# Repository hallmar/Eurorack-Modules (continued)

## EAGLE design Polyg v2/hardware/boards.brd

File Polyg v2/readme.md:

# Polyg v2 8-Voice Midi synth

This new version has a dedicated MIDI thru instead of routing it into the Teensy and back out. 
And it has alot of improvements of the hardware.

[Youtube demo](https://www.youtube.com/watch?v=QhJZFhLLbBc&feature=youtu.be)

[Mouser cart](https://www.mouser.com/ProjectManager/ProjectDetail.aspx?AccessID=3288d77cba)

8 Voice polyphonic synthesizer with selectable Karplus strong(8 voice plucky string synth) or a 8 voice FM synth with square,sine,triangle and sawtooth. It has a basic FM(techincally Phase Modulation, like the DX7) with one Modulator. 
There's an index knob to set the ratio, decay for the operator and the amount of FM applied.

Current hardware uses a high quality 16bit/44.1kHz DAC(CD4334).

It has MIDI IN and MIDI OUT/THRU. It uses the Arturia Standard for DIN to stereo jack, so type B midi.
You can find adapters in almost every synthstore now. 

## Where/how to order
I won't have any PCB's in stock any time soon. This project is pretty much abandoned.
You have my approval of making your own, just remember to credit me.

## Designed With

* Eagle CAD
* Arduino IDE
* Audio System Design Tool for Teensy Audio Library

## Versioning
* 1.0 - [Hardware] Original PCB batch with wrong silkscreen
* 1.1 - [Hardware] v1 of PCBs
* 1.0 - [Software] Original software release
* 2.0 - [Hardware] v2 of PCB is made with improvements
* 2.0 - [Hardware] v2 of firmware is written
## Authors

* **Hallmar Gauti Halldórsson** 

## License
Hardware: cc-by-sa-3.0

Software: MIT license

But if you want to sell or do something with the software or hardware then it'd be nice to include my name and link to my Github somewhere :)

## Acknowledgments
Alot of the inspiration for this project came from the [String Theory](https://makesynthsnotwar.com/modules/stringtheory/) eurorack module by Make Synths Not War.
The original String Theory was programmed by [Jan Ostman](https://janostman.wordpress.com).

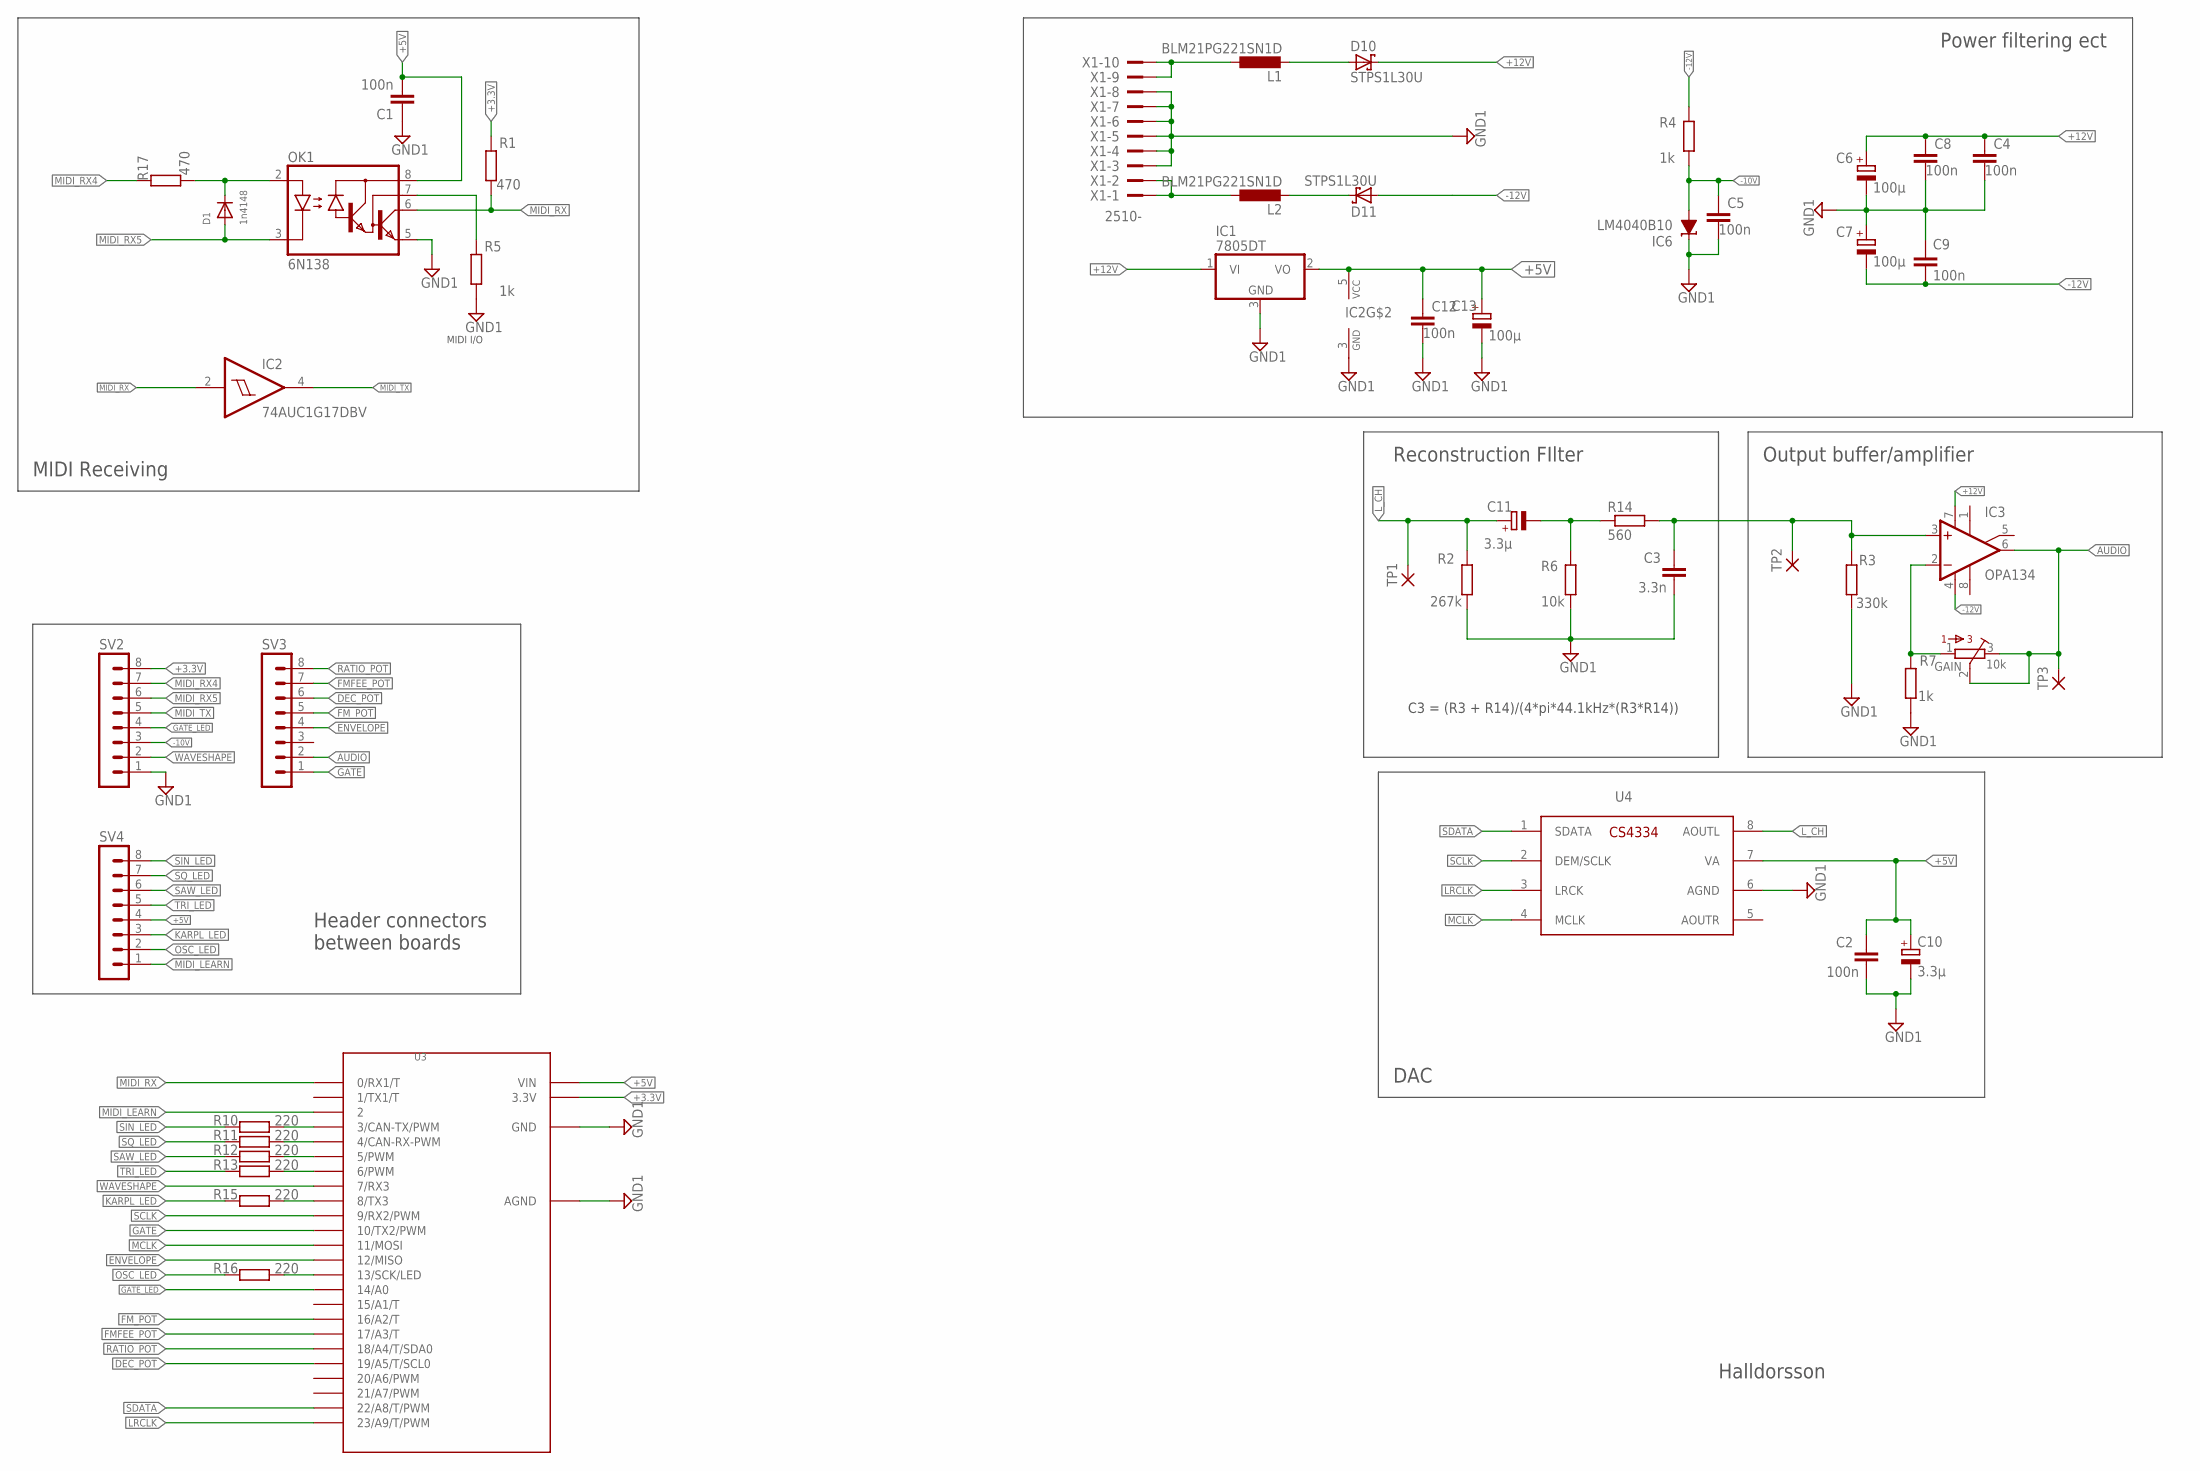
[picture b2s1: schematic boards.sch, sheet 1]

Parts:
C1, C2, C4, C5, C8, C9, C12: 100n; C1206
C3: 3.3n; C1206
C6, C7, C13: 100µ; 153CLV-0505
C10, C11: 3.3µ; 153CLV-0405
D1: 1n4148; SOD-123
D10, D11: STPS1L30U; SMB
GAIN: 10k; BOURNS_3362P_TRIMMER
IC1: 7805DT; TO252
IC2: 74AUC1G17DBV; SOT23-5
IC3: OPA134; SO08
IC6: LM4040B10; DBZ_R-PDSO-G3
L1, L2: BLM21PG221SN1D; L2012C
OK1: 6N138; DIL08
R1, R17: 470; M1206
R2: 267k; M1206
R3: 330k; M1206
R4, R5, R7: 1k; M1206
R6: 10k; M1206
R10, R11, R12, R13, R15, R16: 220; M1206
R14: 560; M1206
SV2, SV3, SV4: MA08-1
TP1, TP2, TP3: 2,54/1,0
U3: TEENSY3.2.BAREBONES; TEENSY3.2_BAREBONES
U4: CS4334; SOIC127P600X175-8N
X1: 2510-; PAK100/2500-10

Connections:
+3.3V: R1.2, SV2.8, U3.3.3V
+5V: C1.2, C2.1, C10.+, C12.1, C13.+, IC1.2 (VO), IC2.5 (VCC), OK1.8 (VCC), SV4.4, U3.VIN, U4.7 (VA)
+12V: C4.1, C6.+, C8.1, D10.C, IC1.1 (VI), IC3.7 (V+)
-10V: C5.1, IC6.2 (A), R4.2, SV2.3
-12V: C7.-, C9.2, D11.A, IC3.4 (V-), R4.1
AUDIO: GAIN.2, GAIN.3, IC3.6 (OUT), SV3.2, TP3.1
DEC_POT: SV3.6, U3.19/A5 (19/A5/T/SCL0)
ENVELOPE: SV3.4, U3.12 (12/MISO)
FMFEE_POT: SV3.7, U3.17/A3 (17/A3/T)
FM_POT: SV3.5, U3.16/A2 (16/A2/T)
GATE: SV3.1, U3.10 (10/TX2/PWM)
GATE_LED: SV2.4, U3.14/A0
GND1: C1.1, C2.2, C3.2, C4.2, C5.2, C6.-, C7.+, C8.2, C9.1, C10.-, C12.2, C13.-, IC1.3 (GND), IC2.3 (GND), IC6.1 (C), OK1.5 (GND), R2.2, R3.2, R5.1, R6.2, R7.2, SV2.1, U3.AGND, U3.GND, U4.6 (AGND), X1.3, X1.4, X1.5, X1.6, X1.7, X1.8
KARPL_LED: R15.2, SV4.3
LRCLK: U3.23/A9 (23/A9/T/PWM), U4.3 (LRCK)
L_CH: C11.+, R2.1, TP1.1, U4.8 (AOUTL)
MCLK: U3.11 (11/MOSI), U4.4 (MCLK)
MIDI_LEARN: SV4.1, U3.2
MIDI_RX: IC2.2 (I), OK1.6 (VO), R1.1, U3.0 (0/RX1/T)
MIDI_RX4: R17.2, SV2.7
MIDI_RX5: D1.A, OK1.3 (C), SV2.6
MIDI_TX: IC2.4 (O), SV2.5
unnamed: C11.-, R6.1, R14.1
unnamed: D1.C, OK1.2 (A), R17.1
unnamed: OK1.7 (VB), R5.2
unnamed: GAIN.1, IC3.2 (-IN), R7.1
unnamed: R16.1, U3.13 (13/SCK/LED)
unnamed: C3.1, IC3.3 (+IN), R3.1, R14.2, TP2.1
unnamed: R10.1, U3.3 (3/CAN-TX/PWM)
unnamed: R11.1, U3.4 (4/CAN-RX-PWM)
unnamed: R12.1, U3.5 (5/PWM)
unnamed: R13.1, U3.6 (6/PWM)
unnamed: R15.1, U3.8 (8/TX3)
unnamed: L1.1, X1.9, X1.10
unnamed: L2.1, X1.1, X1.2
unnamed: D10.A, L1.2
unnamed: D11.C, L2.2
OSC_LED: R16.2, SV4.2
RATIO_POT: SV3.8, U3.18/A4 (18/A4/T/SDA0)
SAW_LED: R12.2, SV4.6
SCLK: U3.9 (9/RX2/PWM), U4.2 (DEM/SCLK)
SDATA: U3.22/A8 (22/A8/T/PWM), U4.1 (SDATA)
SIN_LED: R10.2, SV4.8
SQ_LED: R11.2, SV4.7
TRI_LED: R13.2, SV4.5
WAVESHAPE: SV2.2, U3.7 (7/RX3)

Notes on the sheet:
MIDI I/O
Halldorsson
DAC
Reconstruction FIlter
Header connectors between boards
MIDI Receiving
Power filtering ect
Output buffer/amplifier
C3 = (R3 + R14)/(4*pi*44.1kHz*(R3*R14))

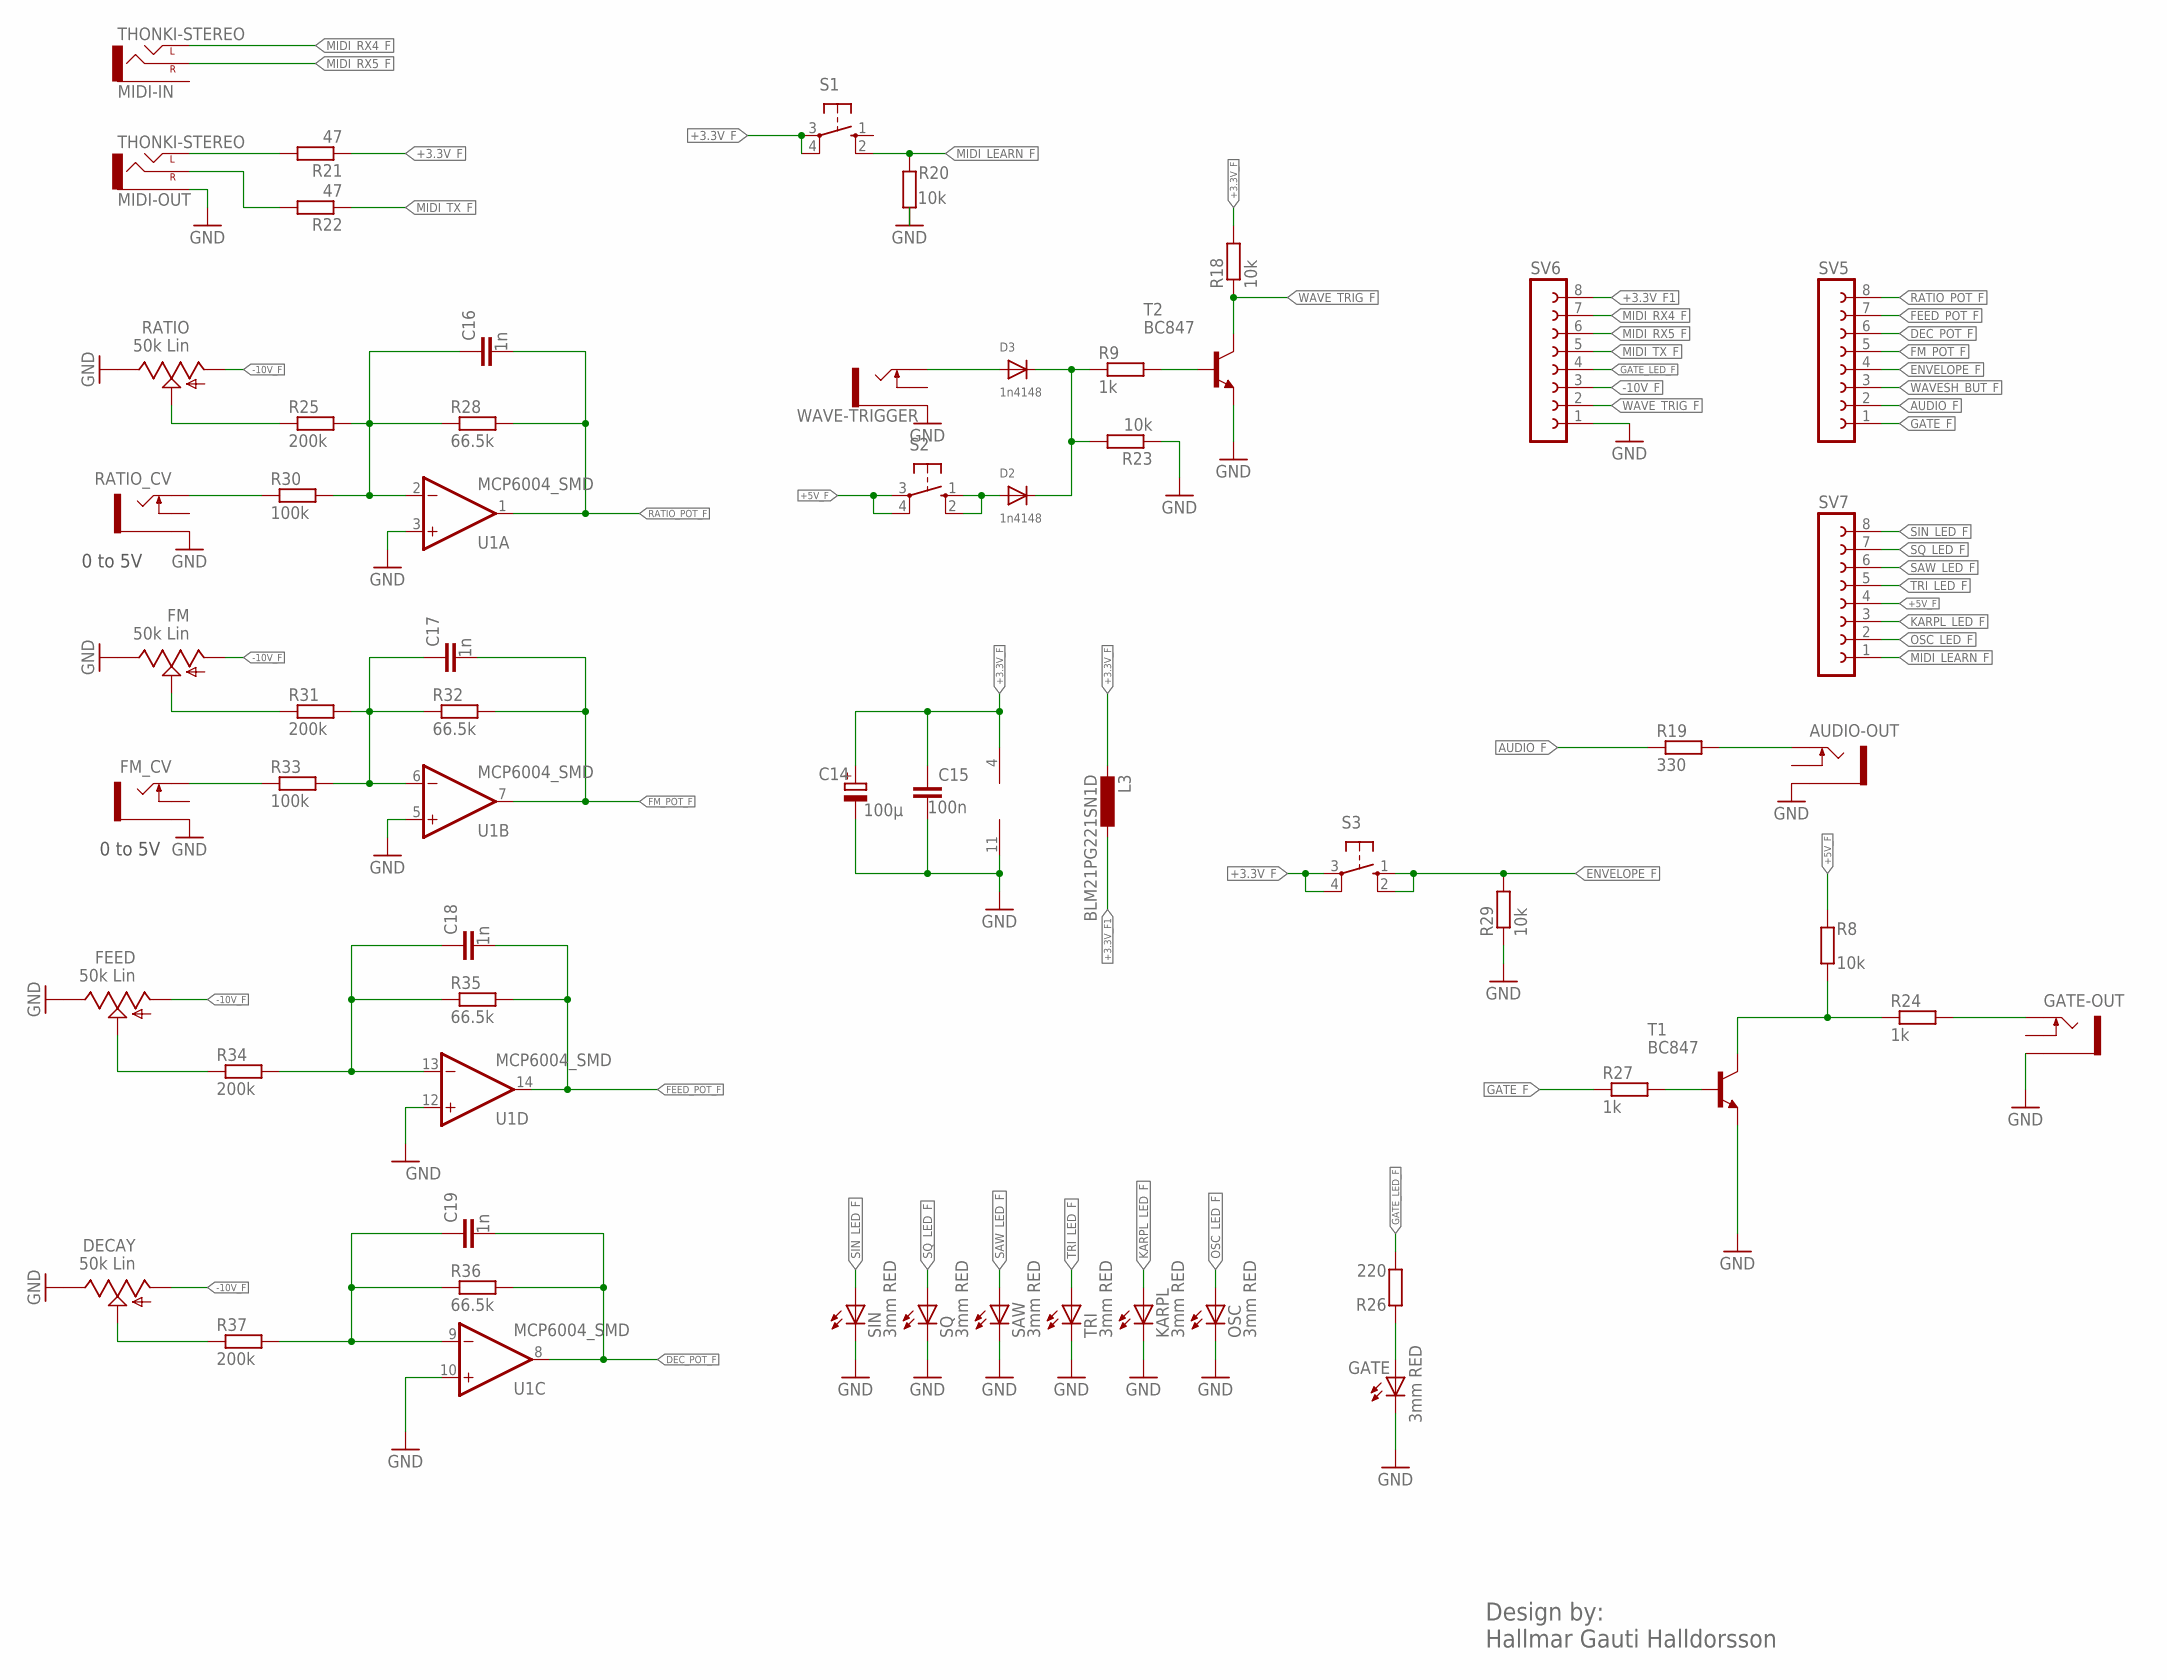
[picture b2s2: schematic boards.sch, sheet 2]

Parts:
AUDIO-OUT: THONKICONNNEW; WQP-PJ301M-12_JACK
C14: 100µ; 153CLV-0505
C15: 100n; C1206
C16, C17, C18, C19: 1n; C1206
D2, D3: 1n4148; SOD-123
DECAY: 50k Lin; 9MM_SNAP-IN_POT
FEED: 50k Lin; 9MM_SNAP-IN_POT
FM: 50k Lin; 9MM_SNAP-IN_POT
FM_CV: THONKICONNNEW; WQP-PJ301M-12_JACK
GATE: 3mm RED; LED3MM
GATE-OUT: THONKICONNNEW; WQP-PJ301M-12_JACK
KARPL: 3mm RED; LED3MM
L3: BLM21PG221SN1D; L2012C
MIDI-IN: THONKI-STEREO; WQP-PJ366ST_JACK
MIDI-OUT: THONKI-STEREO; WQP-PJ366ST_JACK
OSC: 3mm RED; LED3MM
R8, R18, R20, R23, R29: 10k; M1206
R9, R24, R27: 1k; M1206
R19: 330; M1206
R21, R22: 47; M1206
R25, R31, R34, R37: 200k; M1206
R26: 220; M1206
R28, R32, R35, R36: 66.5k; M1206
R30, R33: 100k; M1206
RATIO: 50k Lin; 9MM_SNAP-IN_POT
RATIO_CV: THONKICONNNEW; WQP-PJ301M-12_JACK
S1, S2, S3: 10-XX; B3F-10XX
SAW: 3mm RED; LED3MM
SIN: 3mm RED; LED3MM
SQ: 3mm RED; LED3MM
SV5, SV6, SV7: FE08-1; FE08
T1, T2: BC847; SOT23
TRI: 3mm RED; LED3MM
U1: MCP6004_SMD; SO14
WAVE-TRIGGER: THONKICONNNEW; WQP-PJ301M-12_JACK

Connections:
+3.3V_F: C14.+, C15.1, L3.2, R18.2, R21.1, S1.3, S1.4 (P1), S3.3, S3.4 (P1), U1.4 (V+)
+3.3V_F1: L3.1, SV6.8
+5V_F: R8.1, S2.3, S2.4 (P1), SV7.4
-10V_F: DECAY.1 (A), FEED.1 (A), FM.1 (A), RATIO.1 (A), SV6.3
AUDIO_F: R19.1, SV5.2
B: R27.2, T1.1 (B)
DEC_POT_F: C19.2, R36.2, SV5.6, U1.8 (OUT)
ENVELOPE_F: R29.2, S3.1 (S), S3.2 (S1), SV5.4
FEED_POT_F: C18.2, R35.2, SV5.7, U1.14 (OUT)
FM_POT_F: C17.2, R32.2, SV5.5, U1.7 (OUT)
GATE_F: R27.1, SV5.1
GATE_LED_F: R26.2, SV6.4
GND: AUDIO-OUT.P$3_SLEEVE (SLEEVE), C14.-, C15.2, DECAY.3 (E), FEED.3 (E), FM.3 (E), FM_CV.P$3_SLEEVE (SLEEVE), GATE.K (C), GATE-OUT.P$3_SLEEVE (SLEEVE), KARPL.K (C), MIDI-OUT.P$3_SLEEVE (SLEEVE), OSC.K (C), R20.2, R23.1, R29.1, RATIO.3 (E), RATIO_CV.P$3_SLEEVE (SLEEVE), SAW.K (C), SIN.K (C), SQ.K (C), SV6.1, T1.2 (E), T2.2 (E), TRI.K (C), U1.3 (+IN), U1.5 (+IN), U1.10 (+IN), U1.11 (V-), U1.12 (+IN), WAVE-TRIGGER.P$3_SLEEVE (SLEEVE)
KARPL_LED_F: KARPL.A, SV7.3
MIDI_LEARN_F: R20.1, S1.2 (S1), SV7.1
MIDI_RX4_F: MIDI-IN.P$1_TIP (LEFT), SV6.7
MIDI_RX5_F: MIDI-IN.P$2_SWITCH (RIGHT), SV6.6
MIDI_TX_F: R22.1, SV6.5
unnamed: AUDIO-OUT.P$1_TIP (TIP), R19.2
unnamed: GATE.A, R26.1
unnamed: MIDI-OUT.P$2_SWITCH (RIGHT), R22.2
unnamed: MIDI-OUT.P$1_TIP (LEFT), R21.2
unnamed: R8.2, R24.1, T1.3 (C)
unnamed: R9.2, T2.1 (B)
unnamed: D2.A, S2.1 (S), S2.2 (S1)
unnamed: D3.A, WAVE-TRIGGER.P$1_TIP (TIP)
unnamed: D2.C, D3.C, R9.1, R23.2
unnamed: GATE-OUT.P$1_TIP (TIP), R24.2
unnamed: R25.1, RATIO.2 (S)
unnamed: C16.1, R25.2, R28.1, R30.2, U1.2 (-IN)
unnamed: R30.1, RATIO_CV.P$1_TIP (TIP)
unnamed: FM.2 (S), R31.1
unnamed: C17.1, R31.2, R32.1, R33.2, U1.6 (-IN)
unnamed: FM_CV.P$1_TIP (TIP), R33.1
unnamed: FEED.2 (S), R34.1
unnamed: DECAY.2 (S), R37.1
unnamed: C19.1, R36.1, R37.2, U1.9 (-IN)
unnamed: C18.1, R34.2, R35.1, U1.13 (-IN)
OSC_LED_F: OSC.A, SV7.2
RATIO_POT_F: C16.2, R28.2, SV5.8, U1.1 (OUT)
SAW_LED_F: SAW.A, SV7.6
SIN_LED_F: SIN.A, SV7.8
SQ_LED_F: SQ.A, SV7.7
TRI_LED_F: SV7.5, TRI.A
WAVESH_BUT_F: SV5.3
WAVE_TRIG_F: R18.1, SV6.2, T2.3 (C)

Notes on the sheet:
Design by: Hallmar Gauti Halldorsson
0 to 5V

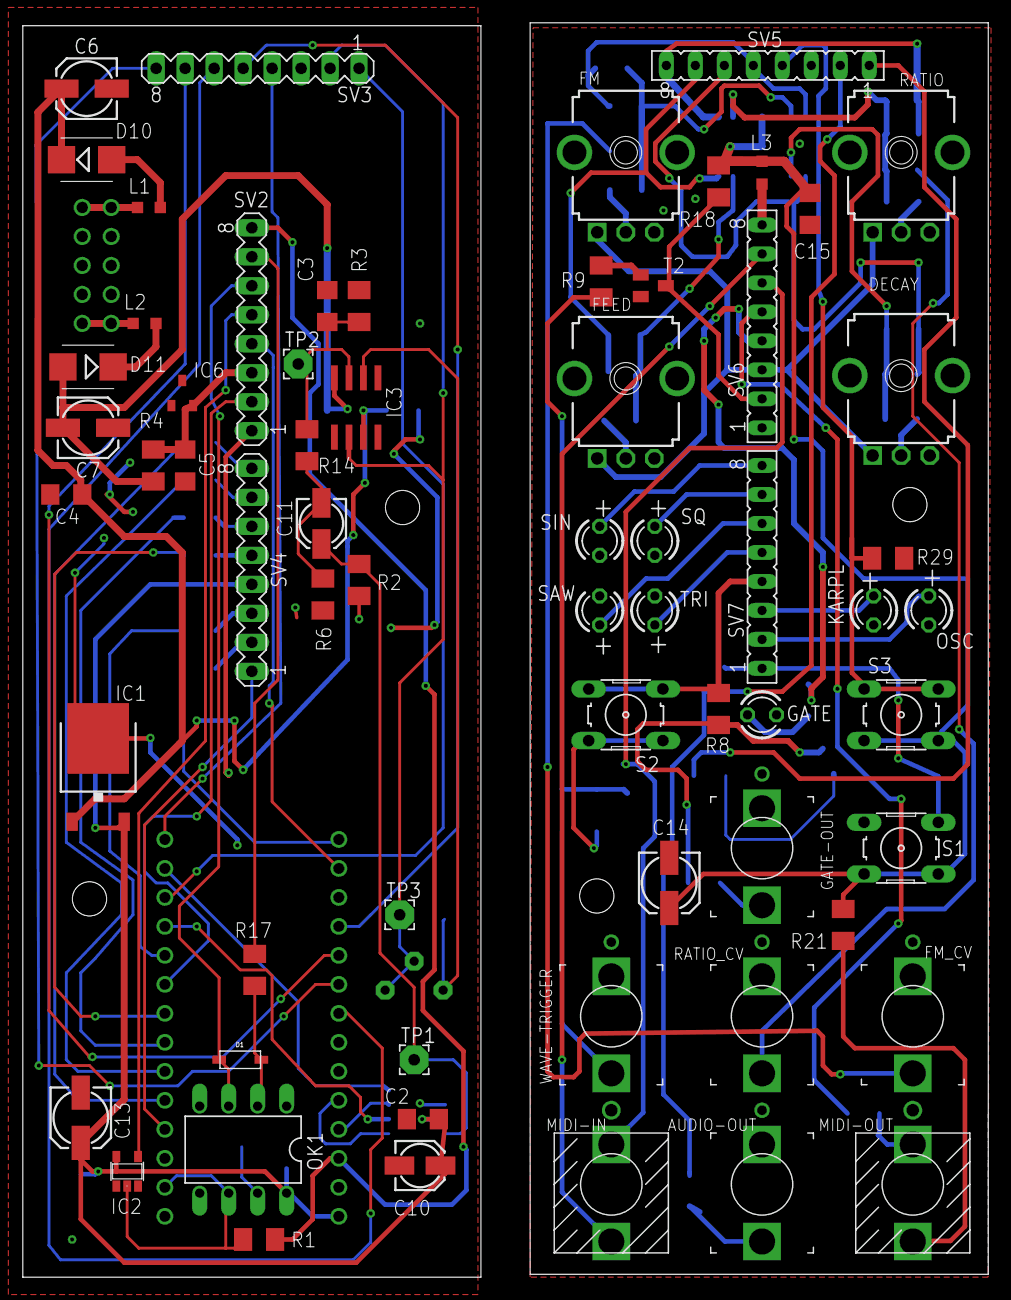
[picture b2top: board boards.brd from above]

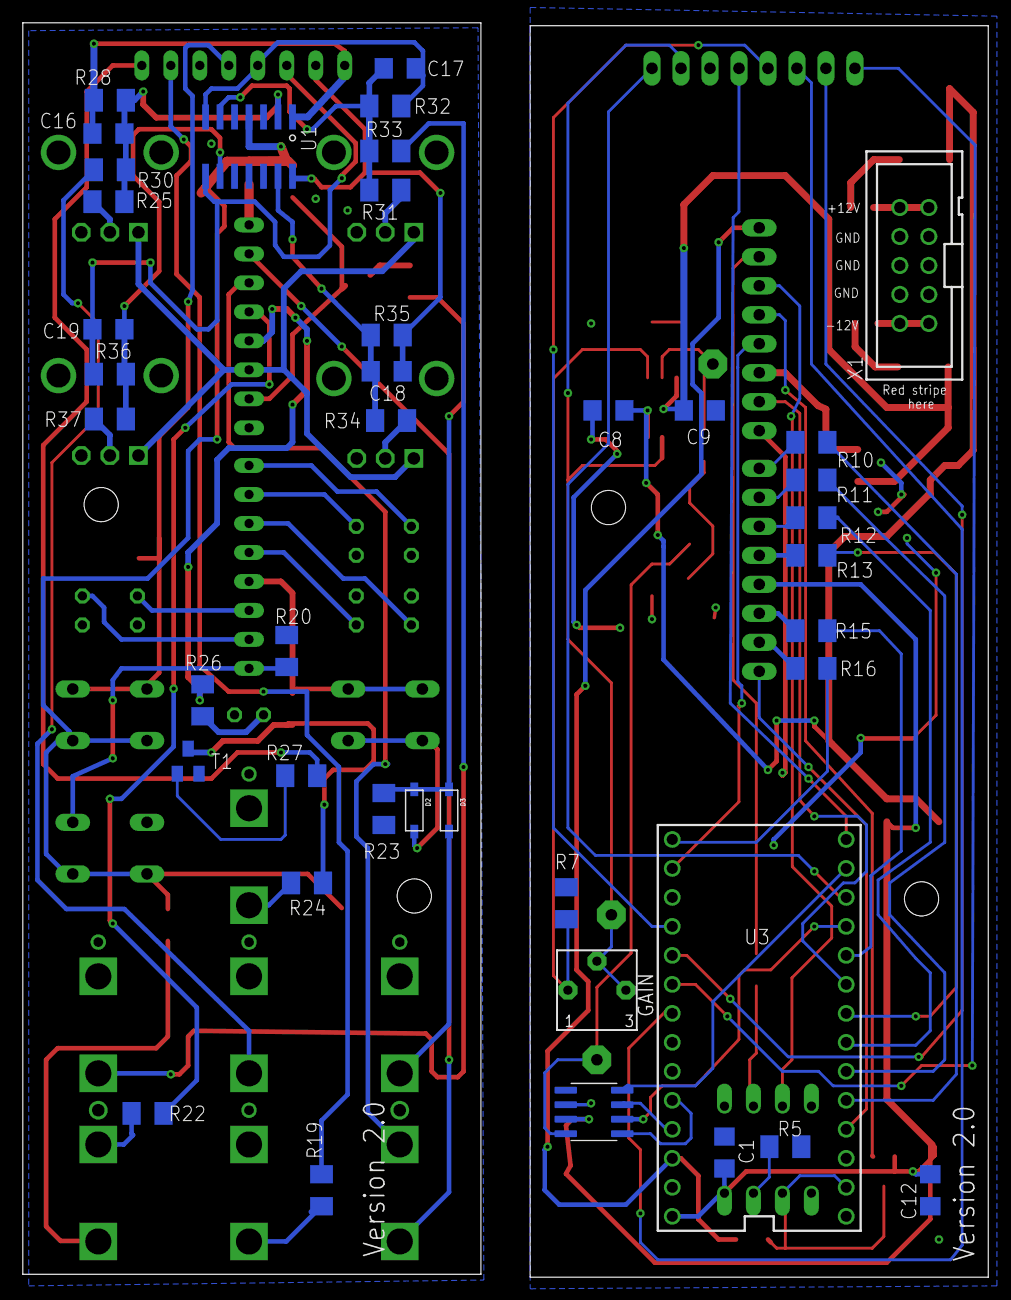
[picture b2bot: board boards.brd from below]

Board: 2 copper layers, 84.6 x 109.9 mm, 106 parts (41 on the bottom side), 91 nets.

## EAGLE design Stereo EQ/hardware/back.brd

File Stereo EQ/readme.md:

# Stereo EQ 
Simply a dual Simple-EQ from Music Thing Modular.
I edited some values but otherwise it's just the basic schematic from Douglas Self's Small Signal Audio Design.

[Mouser Cart](https://www.mouser.com/ProjectManager/ProjectDetail.aspx?AccessID=fd9e850b66)
## Where/how to order
Might sell some when it's ready and I have a working prototype. 

## Designed With

* Eagle CAD

## Versioning

## Authors

* PCB design by **Hallmar Gauti Halldórsson** 

## License
Hardware: cc-by-sa-3.0

## Acknowledgments
The inspiration for this was the Simple EQ by Music Thing Modular. I liked how simple the circuit is and how useful it would be if it was for stereo.

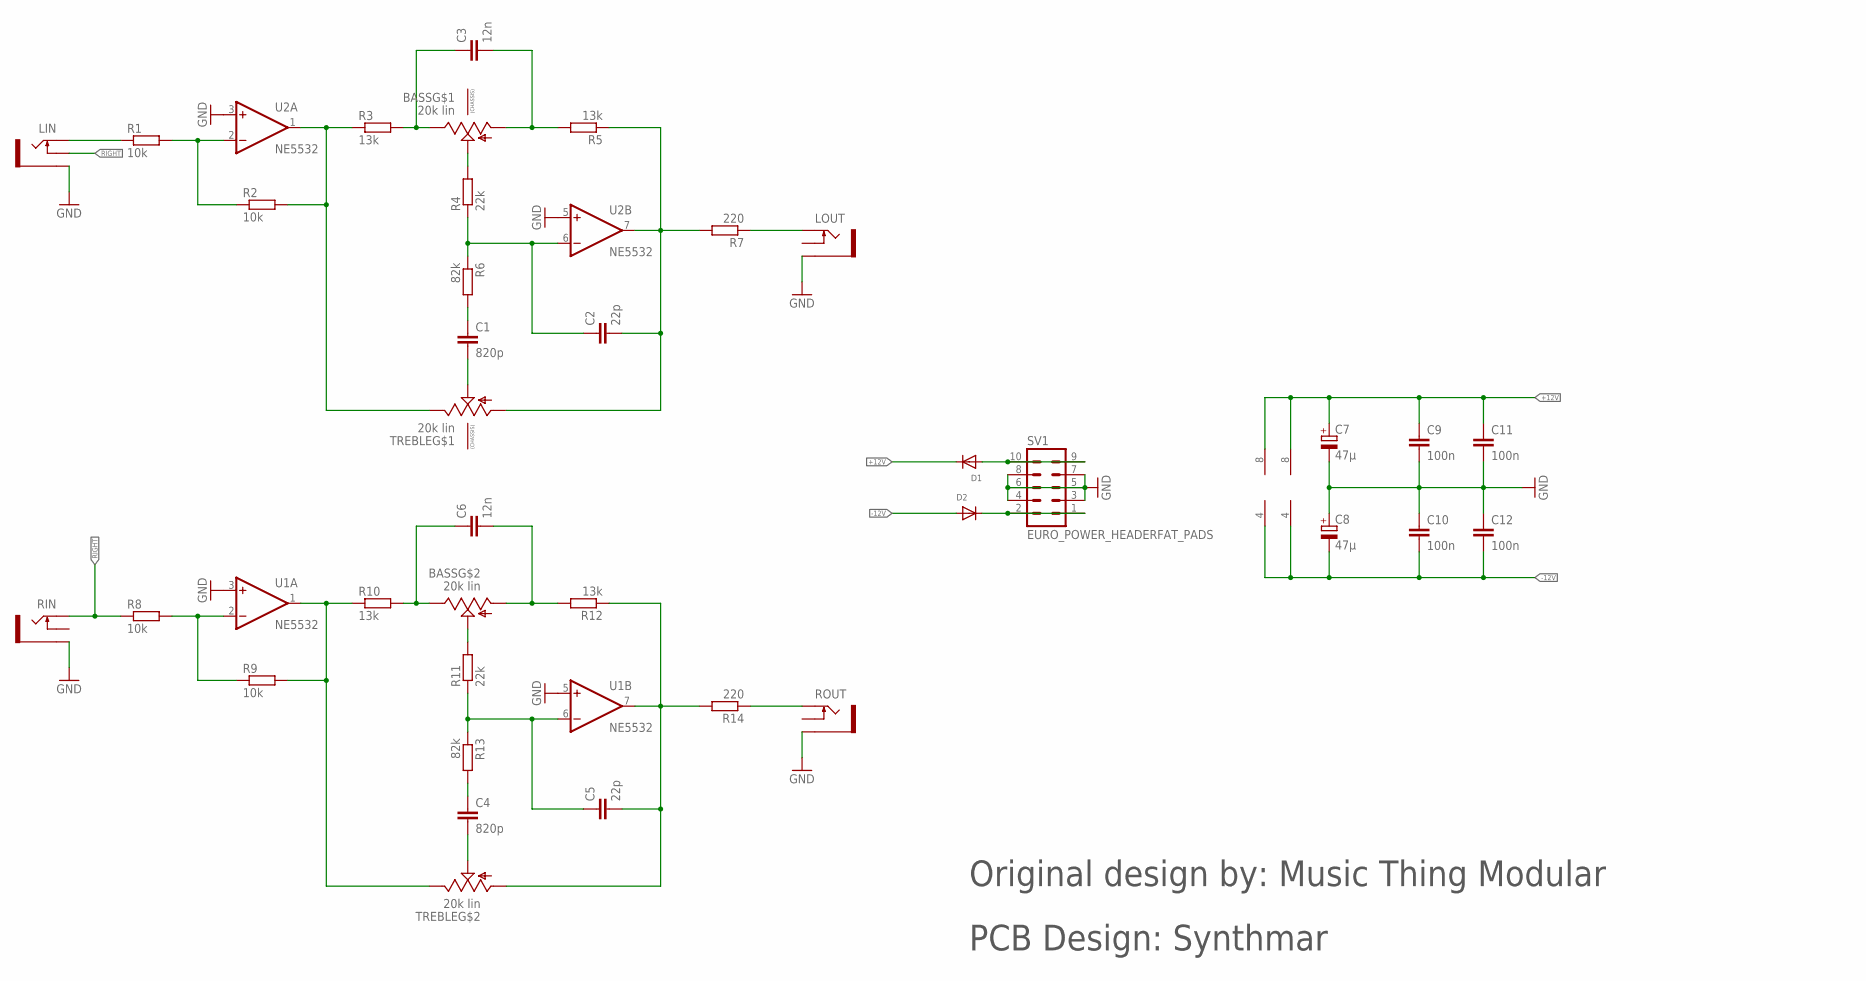
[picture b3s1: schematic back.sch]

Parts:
BASS: 20k lin; DUAL_9MM_SNAP-IN_POT
C1, C4: 820p; C1206
C2, C5: 22p; C1206
C3, C6: 12n; C1206
C7, C8: 47µ; 153CLV-0505
C9, C10, C11, C12: 100n; C1206
D1, D2: DIODESOD-323F; SOD-323F
LIN: THONKICONN16PJ138; WQP-PJ301M-12_JACK
LOUT: THONKICONN16PJ138; WQP-PJ301M-12_JACK
R1, R2, R8, R9: 10k; M1206
R3, R5, R10, R12: 13k; M1206
R4, R11: 22k; M1206
R6, R13: 82k; M1206
R7, R14: 220; M1206
RIN: THONKICONN16PJ138; WQP-PJ301M-12_JACK
ROUT: THONKICONN16PJ138; WQP-PJ301M-12_JACK
SV1: EURO_POWER_HEADERFAT_PADS; EURO_PWR_HEADER_FAT
TREBLE: 20k lin; DUAL_9MM_SNAP-IN_POT
U1, U2: NE5532; SO08

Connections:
+12V: C7.+, C9.1, C11.1, D1.C, U1.8 (V+), U2.8 (V+)
-12V: C8.-, C10.2, C12.2, D2.A, U1.4 (V-), U2.4 (V-)
GND: C7.-, C8.+, C9.2, C10.1, C11.2, C12.1, LIN.P$3_SLEEVE (SLEEVE), LOUT.P$3_SLEEVE (SLEEVE), RIN.P$3_SLEEVE (SLEEVE), ROUT.P$3_SLEEVE (SLEEVE), SV1.3, SV1.4, SV1.5, SV1.6, SV1.7, SV1.8, U1.3 (+IN), U1.5 (+IN), U2.3 (+IN), U2.5 (+IN)
unnamed: BASS.3 (E), C3.1, R3.2
unnamed: R2.2, R3.1, TREBLE.3 (E), U2.1 (OUT)
unnamed: R1.2, R2.1, U2.2 (-IN)
unnamed: C2.2, R5.1, R7.2, TREBLE.1 (A), U2.7 (OUT)
unnamed: BASS.1 (A), C3.2, R5.2
unnamed: BASS.2 (S), R4.2
unnamed: LOUT.P$1_TIP (TIP), R7.1
unnamed: C1.1, R6.2
unnamed: C1.2, TREBLE.2 (S)
unnamed: C2.1, R4.1, R6.1, U2.6 (-IN)
unnamed: LIN.P$1_TIP (TIP), R1.1
unnamed: BASS.3B (E), C6.1, R10.2
unnamed: R9.2, R10.1, TREBLE.3B (E), U1.1 (OUT)
unnamed: R8.2, R9.1, U1.2 (-IN)
unnamed: C5.2, R12.1, R14.2, TREBLE.1B (A), U1.7 (OUT)
unnamed: BASS.1B (A), C6.2, R12.2
unnamed: BASS.2B (S), R11.2
unnamed: C4.1, R13.2
unnamed: C4.2, TREBLE.2B (S)
unnamed: C5.1, R11.1, R13.1, U1.6 (-IN)
unnamed: R14.1, ROUT.P$1_TIP (TIP)
unnamed: D1.A, SV1.9, SV1.10
unnamed: D2.C, SV1.1, SV1.2
RIGHT: LIN.P$2_SWITCH (SWITCH), R8.1, RIN.P$1_TIP (TIP)

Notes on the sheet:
Original design by: Music Thing Modular
PCB Design: Synthmar

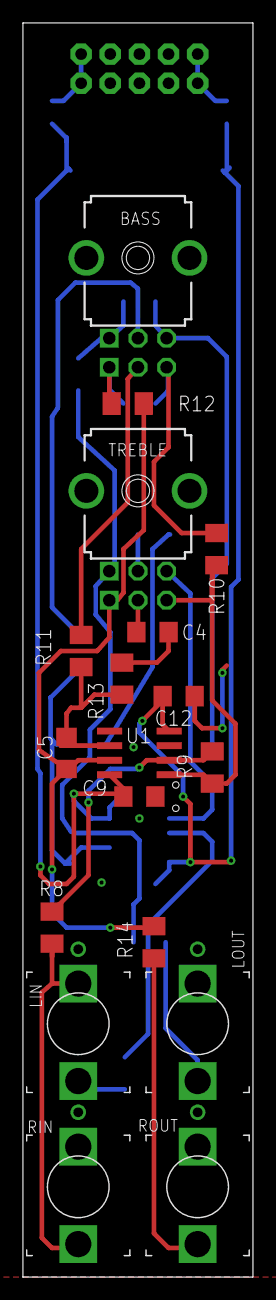
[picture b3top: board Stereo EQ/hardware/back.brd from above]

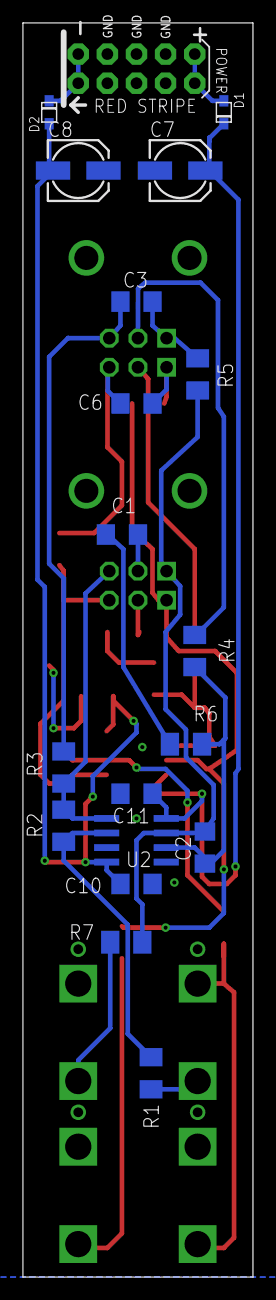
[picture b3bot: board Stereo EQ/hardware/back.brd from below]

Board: 2 copper layers, 20.1 x 109.4 mm, 37 parts (19 on the bottom side), 27 nets.

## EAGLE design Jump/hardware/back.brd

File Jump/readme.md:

# Jump
It's a module that can transport 11 signals from one point to another point. Super useful if you have two eurorack cases. 
[Mouser Cart](https://www.mouser.com/ProjectManager/ProjectDetail.aspx?AccessID=3f3b3b9838), the mouser cart contains parts for two of these modules. Since you'd obviously need two of them to go from point A to point B.

## Where/how to order
Not selling any PCB's for this until later..

## Designed With

* Eagle CAD

## Versioning

## Authors

* Design by **Hallmar Gauti Halldórsson** 

## License
Hardware: cc-by-sa-3.0

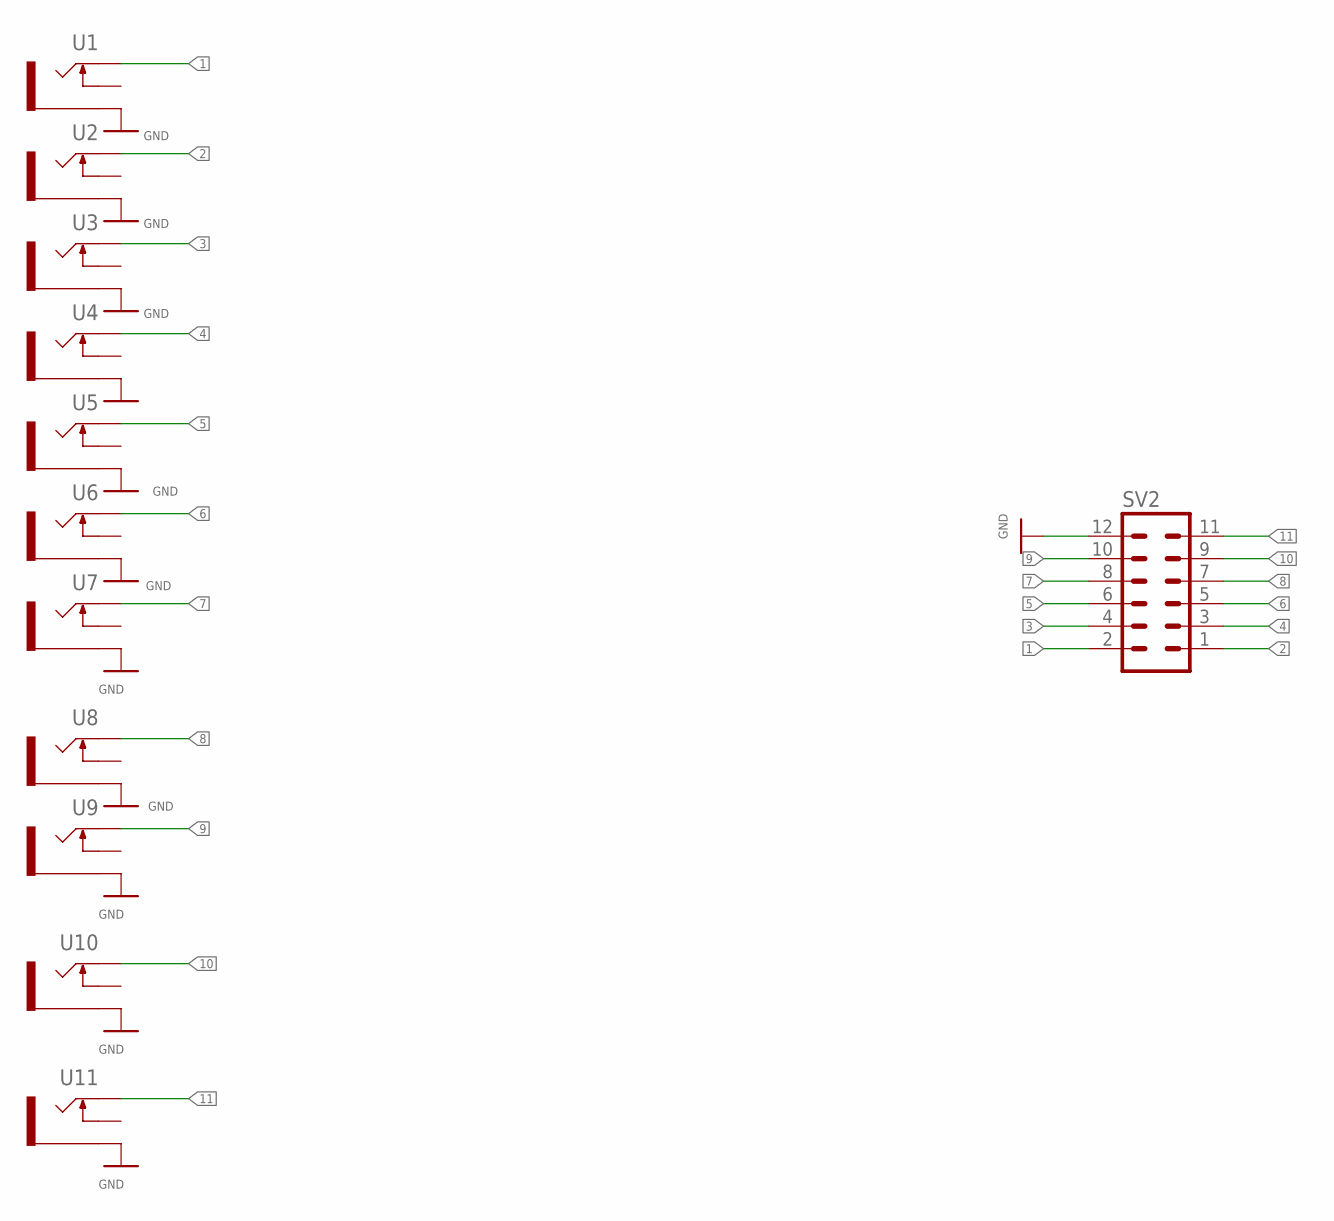
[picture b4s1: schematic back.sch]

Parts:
SV2: MA06-2
U1, U3, U4, U5, U6, U7, U8, U9, U10, U11: THONKICONNNEW; WQP-PJ301M-12_JACK
U2: THONKICONN16PJ138; WQP-PJ301M-12_JACK

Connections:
1: SV2.2, U1.P$1_TIP (TIP)
2: SV2.1, U2.P$1_TIP (TIP)
3: SV2.4, U3.P$1_TIP (TIP)
4: SV2.3, U4.P$1_TIP (TIP)
5: SV2.6, U5.P$1_TIP (TIP)
6: SV2.5, U6.P$1_TIP (TIP)
7: SV2.8, U7.P$1_TIP (TIP)
8: SV2.7, U8.P$1_TIP (TIP)
9: SV2.10, U9.P$1_TIP (TIP)
10: SV2.9, U10.P$1_TIP (TIP)
11: SV2.11, U11.P$1_TIP (TIP)
GND: SV2.12, U1.P$3_SLEEVE (SLEEVE), U2.P$3_SLEEVE (SLEEVE), U3.P$3_SLEEVE (SLEEVE), U4.P$3_SLEEVE (SLEEVE), U5.P$3_SLEEVE (SLEEVE), U6.P$3_SLEEVE (SLEEVE), U7.P$3_SLEEVE (SLEEVE), U8.P$3_SLEEVE (SLEEVE), U9.P$3_SLEEVE (SLEEVE), U10.P$3_SLEEVE (SLEEVE), U11.P$3_SLEEVE (SLEEVE)

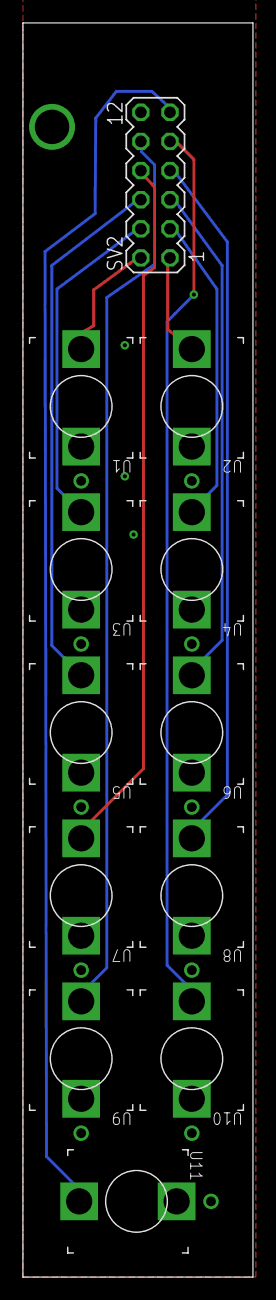
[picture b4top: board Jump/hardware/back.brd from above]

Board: 2 copper layers, 20.1 x 109.4 mm, 12 parts (0 on the bottom side), 12 nets.
